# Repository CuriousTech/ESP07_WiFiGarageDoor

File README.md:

# ESP07_WiFiGarageDoor

This is USB powered and uses an analog IR range sensor (20 to 150cm) to detect door position on the top rail, and an HC-SR05 for the car, DC sink output for opener, OLED display, and DHT22 for temp and rh.
  
Note:  Pin 1 of the OLED is GND (these came from eBay, so I needed to use them for something).  
  
Here's [a small case](http://www.allelectronics.com/make-a-store/item/mbu-906/utility-case-2.74-x-1.99-x-0.83/1.html) that it fits nicely in.

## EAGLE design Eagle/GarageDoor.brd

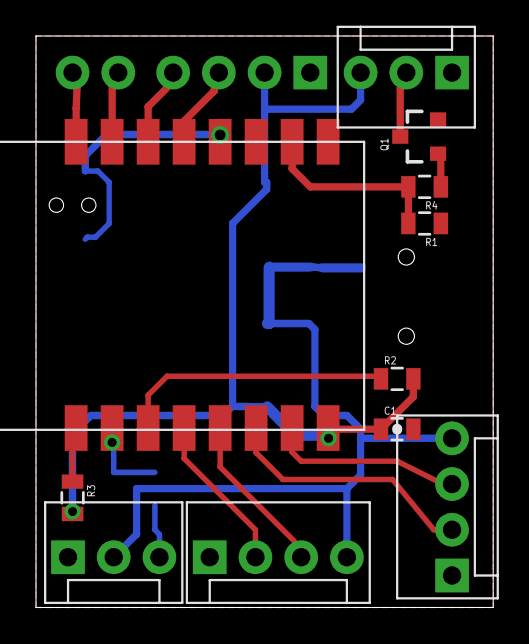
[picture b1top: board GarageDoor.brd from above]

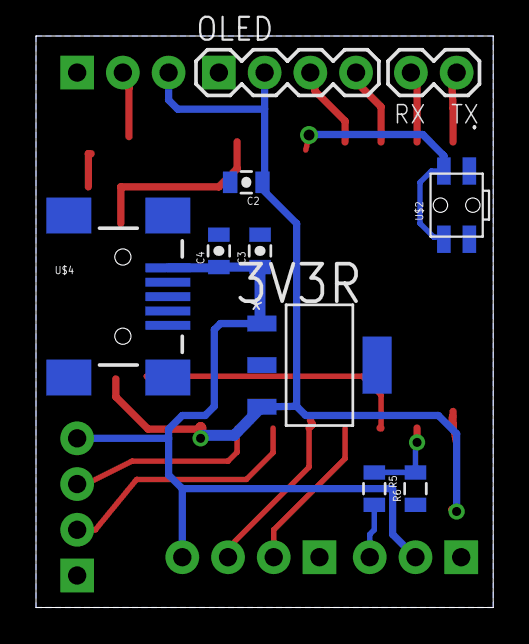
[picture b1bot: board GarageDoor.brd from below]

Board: 2 copper layers, 25.4 x 31.8 mm, 21 parts (10 on the bottom side), 19 nets.

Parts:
3V3R: MCP1824ST-3302E/DB; SOT230P700X180-4N
.: 1X02
C1, C2, C3: 0.1uF; 0805-CAP
C4: 1uF; 0805-CAP
JP1, JP3: MOLEX-1X4
JP2, JP6: MOLEX-1X3
OLED: 1X04
Q1: SOT23-3
R1, R2, R3: 10K; 0805
R4: 1K; 0805
R5: 5K6; 0805
R6: 4K7; 0805
U$1: ESP-07/12
U$2: SIDE-TACT
U$4: USB-MINIB-5PIN; USB-MINIB

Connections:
3V3: 3V3R.3, C1.1, C2.1, JP6.3, OLED.2, R2.2, R3.2, U$1.VCC
+5V: 3V3R.1, C3.1, C4.1, JP1.4, JP2.2, JP3.4, U$4.VBUS
ADC: R5.1, R6.2, U$1.ADC
ANA: JP2.3, R5.2
GND: 3V3R.2, 3V3R.4, C1.2, C2.2, C3.2, C4.2, JP1.1, JP2.1, JP3.1, JP6.1, OLED.1, Q1.2, R1.1, R6.1, U$1.GND, U$2.3, U$2.4, U$4.GND, U$4.MTN1, U$4.MTN2, U$4.MTN3, U$4.MTN4
ICSPCLK: R3.1, U$1.REST
IO0: U$1.GPIO0, U$2.1, U$2.2
IO12: JP1.2, U$1.GPIO12
IO13: JP1.3, U$1.GPIO13
IO14: JP3.3, U$1.GPIO14
IO15: R1.2, R4.2, U$1.GPIO15
IO16: JP3.2, U$1.GPIO16
unnamed: JP6.2, Q1.3
unnamed: OLED.4, U$1.GPIO4
unnamed: OLED.3, U$1.GPIO5
unnamed: Q1.1, R4.1
unnamed: R2.1, U$1.CH_PD
RXD: ..2, U$1.RXD
TXD: ..1, U$1.TXD

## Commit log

2015-12-21 Rename GarageDoor.ino to Arduino/GarageDoor.ino
2015-12-21 Rename WiFiManager.cpp to Arduino/WiFiManager.cpp
2015-12-21 Rename WiFiManager.h to Arduino/WiFiManager.h
2015-12-21 Rename font.h to Arduino/font.h
2015-12-21 Rename icons.h to Arduino/icons.h
2015-12-21 Rename ssd1306_i2i.cpp to Arduino/ssd1306_i2i.cpp
2016-01-06 Changed to positive side sensor control
2016-01-21 It's all good
2016-01-27 Flipped screen
2016-01-27 Added door close timeout
2016-01-29 Changed to NPN output
2016-01-29 Changed to positive pulse
2016-01-31 Car distance was flipped
2016-02-04 Bugs found after power outages
2016-02-04 Updated for new watchdog
2016-02-10 Another 2.0.0 fix
2016-02-20 Added HC-SR04 for car sensing
2016-02-20 Checks for SSID while in soft AP mode
2016-03-09 Using JQuery for event pushes
2016-03-10 Simplified, added DHT22
2016-03-10 Added DHT22
2016-03-13 Switched to esp time
2016-03-13 Fixed DST
2016-03-13 cleanup
2016-03-13 cleaup
2016-03-15 More cleanup
2016-05-03 Updated for TimeLib fix for IDE 1.6.8
2016-05-03 Udpate to TimeLib for IDE 1.6.8
2016-05-05 Moved event lib
2016-05-25 Added PushBullet push
2016-06-10 Moved ssd1306 to lib
2016-06-22 Updated page design
2016-06-25 Fixed password report
2016-09-18 Added delay timer
2016-09-21 Added RunningMedian for smoothing rangefinders
2016-09-22 Switched to ESPAsyncWebServer
2016-09-22 Switched to ESPAsyncWebServer retry
2016-10-15 changed to WebSocket
2016-10-15 build note
2016-10-15 Added WebSockets
2016-10-26 Added settings page
2016-10-26 Changes for settings page
2016-11-10 key not in scope
2016-11-10 duplicate label
2016-11-10 copied an id
2016-11-28 Auto display on, number display
2016-12-03 Async remote pulse, IR distance in CM
2017-01-13 Broke SSID list and change key
2017-01-13 Changed path for security
2017-03-02 smoother temps, added OTA
2017-07-06 Fix for printfAll bug in latest WebSocket
2018-05-01 Removed a printf, flipped screen
2018-05-01 Added favicon
2023-01-26 Too many changes
2023-02-03 Json prefix change
2023-02-03 Copied wrong file
2023-02-03 Removed json prefix
2025-05-25 Can use TZ=0 for GMT instead of local+DST

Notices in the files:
parts and their libraries:
SparkFun-Connectors: Licensing: Creative Commons ShareAlike 4.0 International - https://creativecommons.org/licenses/by-sa/4.0
